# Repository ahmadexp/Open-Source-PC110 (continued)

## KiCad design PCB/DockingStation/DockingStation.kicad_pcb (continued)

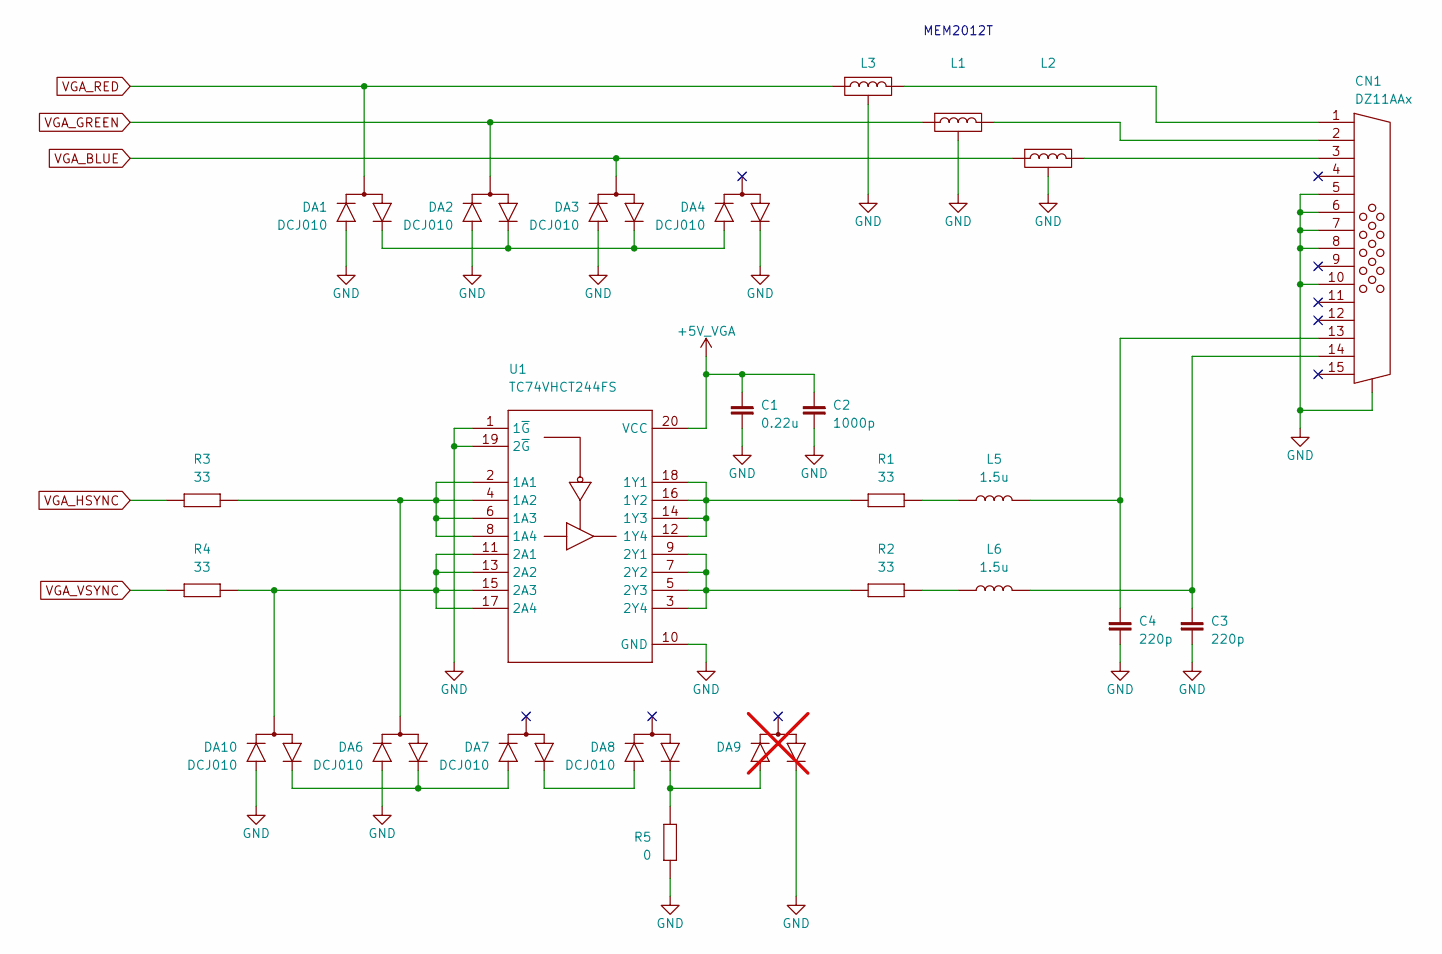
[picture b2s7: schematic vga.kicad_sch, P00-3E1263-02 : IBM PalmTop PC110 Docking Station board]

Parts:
C1: 0.22u
C2: 1000p
C3, C4: 220p
CN1: DZ11AAx
DA1, DA2, DA3, DA4, DA6, DA7, DA8, DA10: DCJ010
DA9: not fitted
L1, L2, L3: (no value)
L5, L6: 1.5u
R1, R2, R3, R4: 33
R5: 0
U1: TC74VHCT244FS

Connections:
+5V_VGA: C1.2, C2.2, U1.20 (VCC); also elsewhere on the board
GND: C1.1, C2.1, C3.2, C4.2, CN1.0, CN1.5, CN1.6, CN1.7, CN1.8, CN1.10, DA1.1 (A), DA2.1 (A), DA3.1 (A), DA4.2 (C), DA6.1 (A), DA9.2 (C), DA10.1 (A), L1.3, L2.3, L3.3, R5.1, U1.1 (1~G), U1.10 (GND), U1.19 (2~G); also elsewhere on the board
unnamed: C3.1, CN1.14, L6.2
unnamed: C4.1, CN1.13, L5.2
unnamed: CN1.1, L3.2
unnamed: CN1.2, L1.2
unnamed: CN1.3, L2.2
unnamed: DA1.2 (C), DA2.2 (C), DA3.2 (C), DA4.1 (A)
unnamed: DA6.3 (CA), R3.2, U1.2 (1A1), U1.4 (1A2), U1.6 (1A3), U1.8 (1A4)
unnamed: DA7.2 (C), DA8.1 (A)
unnamed: DA8.2 (C), DA9.1 (A), R5.2
unnamed: DA6.2 (C), DA7.1 (A), DA10.2 (C)
unnamed: DA10.3 (CA), R4.2, U1.11 (2A1), U1.13 (2A2), U1.15 (2A3), U1.17 (2A4)
unnamed: L5.1, R1.2
unnamed: L6.1, R2.2
unnamed: R1.1, U1.12 (1Y4), U1.14 (1Y3), U1.16 (1Y2), U1.18 (1Y1)
unnamed: R2.1, U1.3 (2Y4), U1.5 (2Y3), U1.7 (2Y2), U1.9 (2Y1)
VGA_BLUE: DA3.3 (CA), L2.1; also elsewhere on the board
VGA_GREEN: DA2.3 (CA), L1.1; also elsewhere on the board
VGA_HSYNC: R3.1; also elsewhere on the board
VGA_RED: DA1.3 (CA), L3.1; also elsewhere on the board
VGA_VSYNC: R4.1; also elsewhere on the board

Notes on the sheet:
MEM2012T

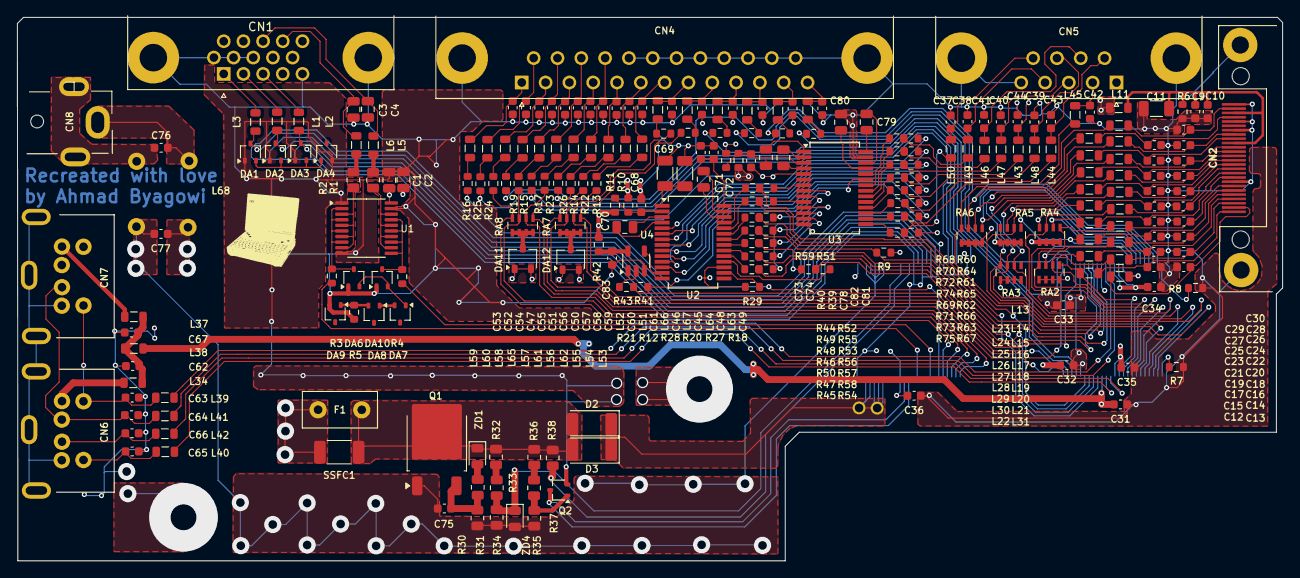
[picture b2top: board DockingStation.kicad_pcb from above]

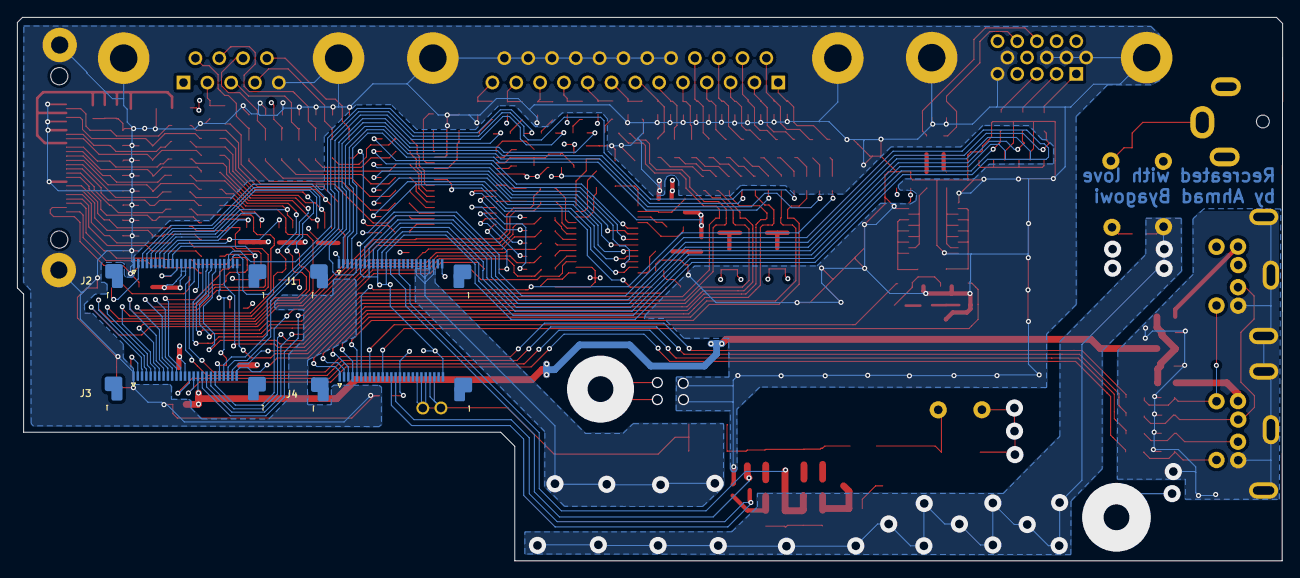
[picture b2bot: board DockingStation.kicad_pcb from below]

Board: 4 copper layers, 147.2 x 63.2 mm, 254 parts (4 on the bottom side), 220 nets.

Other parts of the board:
G1: LOGO; logo

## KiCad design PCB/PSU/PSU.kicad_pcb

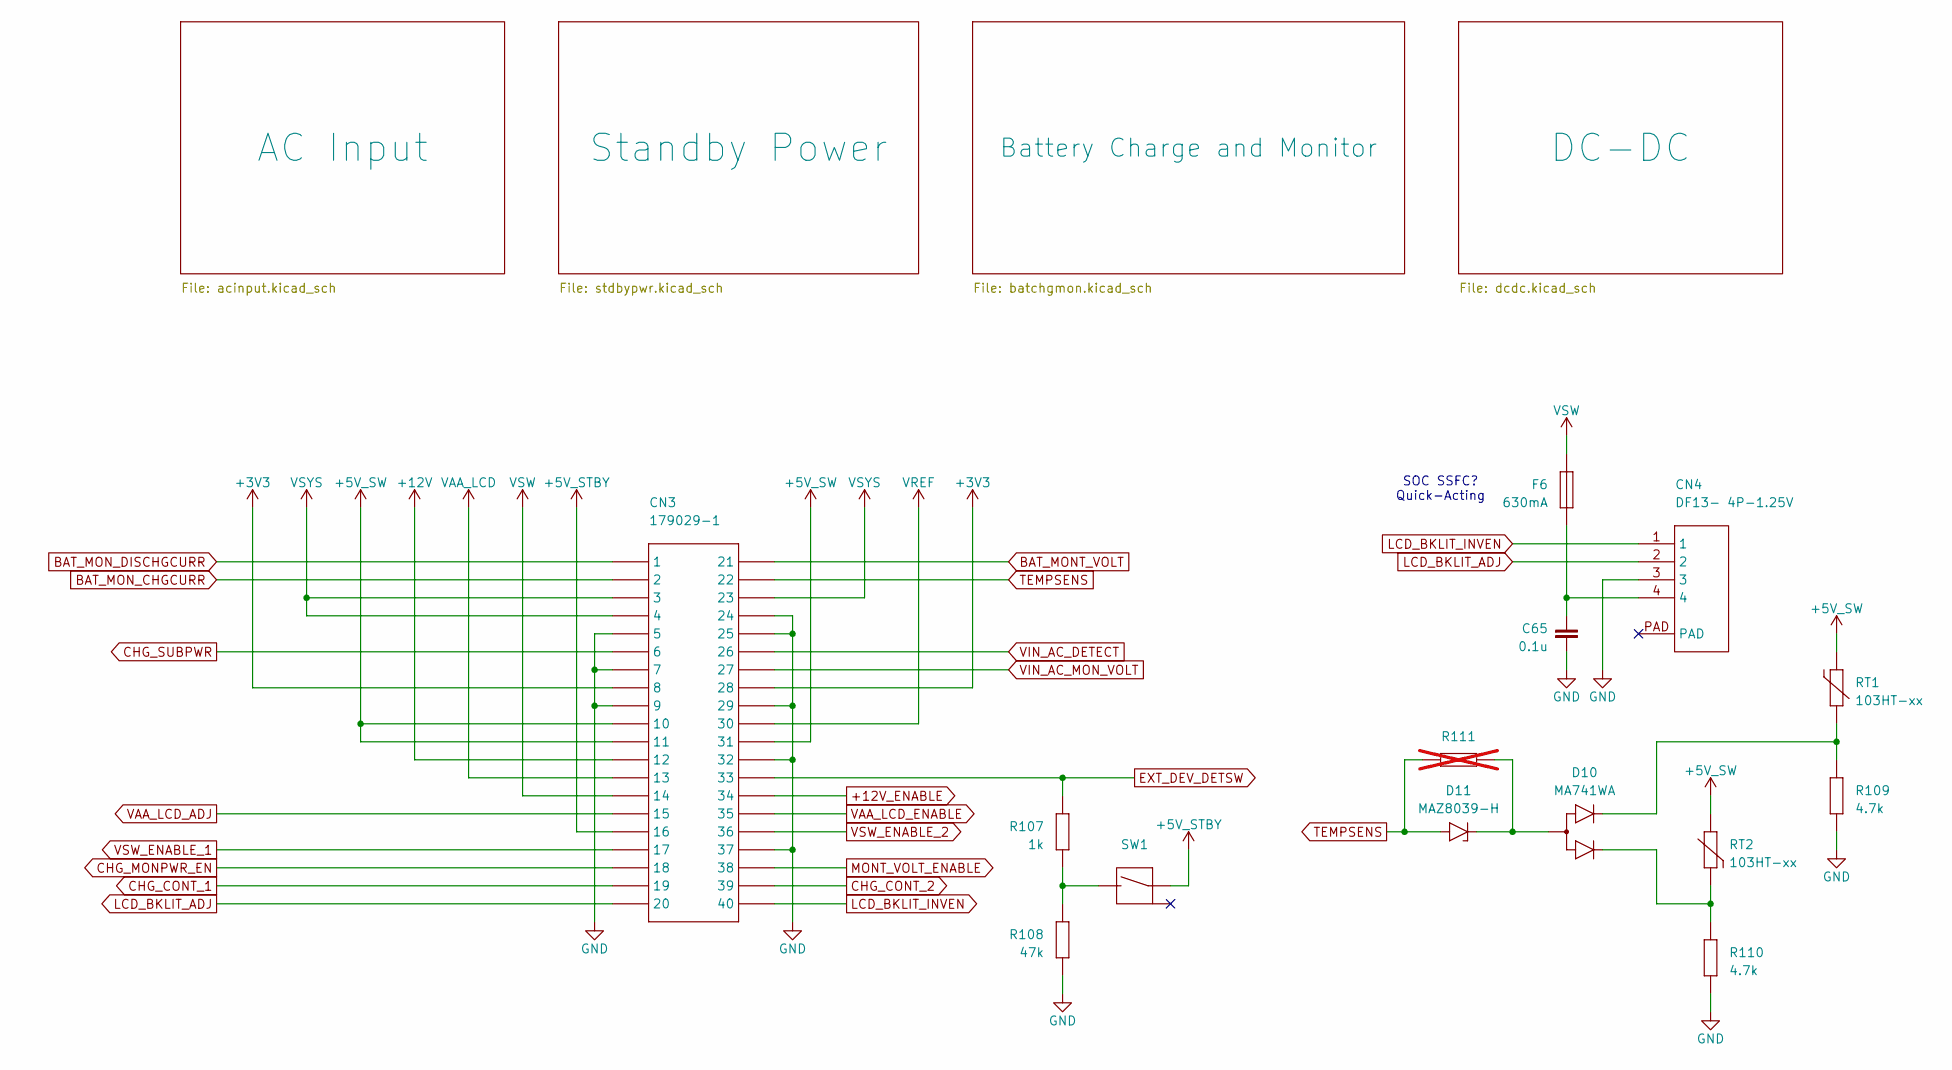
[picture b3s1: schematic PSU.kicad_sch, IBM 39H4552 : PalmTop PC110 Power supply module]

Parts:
C65: 0.1u
CN3: 179029-1
CN4: DF13- 4P-1.25V
D10: MA741WA
D11: MAZ8039-H
F6: 630mA
R107: 1k
R108: 47k
R109, R110: 4.7k
R111: not fitted
RT1, RT2: 103HT-xx
SW1: (no value)

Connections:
+3V3: CN3.8, CN3.28; also elsewhere on the board
+5V_STBY: CN3.16, SW1.1; also elsewhere on the board
+5V_SW: CN3.10, CN3.11, CN3.31, RT1.2, RT2.1; also elsewhere on the board
+12V: CN3.12; also elsewhere on the board
+12V_ENABLE: CN3.34; also elsewhere on the board
BAT_MONT_VOLT: CN3.21; also elsewhere on the board
BAT_MON_CHGCURR: CN3.2; also elsewhere on the board
BAT_MON_DISCHGCURR: CN3.1; also elsewhere on the board
CHG_CONT_1: CN3.19; also elsewhere on the board
CHG_CONT_2: CN3.39; also elsewhere on the board
CHG_MONPWR_EN: CN3.18; also elsewhere on the board
CHG_SUBPWR: CN3.6; also elsewhere on the board
EXT_DEV_DETSW: CN3.33, R107.2; also elsewhere on the board
GND: C65.1, CN3.5, CN3.7, CN3.9, CN3.24, CN3.25, CN3.29, CN3.32, CN3.37, CN4.3, R108.2, R109.1, R110.1; also elsewhere on the board
LCD_BKLIT_ADJ: CN3.20, CN4.2
LCD_BKLIT_INVEN: CN3.40, CN4.1
MONT_VOLT_ENABLE: CN3.38; also elsewhere on the board
unnamed: C65.2, CN4.4, F6.1
unnamed: D10.2 (A), D11.1 (C), R111.1
unnamed: D10.1 (C1), R110.2, RT2.2
unnamed: D10.3 (C2), R109.2, RT1.1
unnamed: R107.1, R108.1, SW1.2
TEMPSENS: CN3.22, D11.2 (A), R111.2
VAA_LCD: CN3.13; also elsewhere on the board
VAA_LCD_ADJ: CN3.15; also elsewhere on the board
VAA_LCD_ENABLE: CN3.35; also elsewhere on the board
VIN_AC_DETECT: CN3.26; also elsewhere on the board
VIN_AC_MON_VOLT: CN3.27; also elsewhere on the board
VREF: CN3.30; also elsewhere on the board
VSW: CN3.14, F6.2; also elsewhere on the board
VSW_ENABLE_1: CN3.17; also elsewhere on the board
VSW_ENABLE_2: CN3.36; also elsewhere on the board
VSYS: CN3.3, CN3.4, CN3.23; also elsewhere on the board

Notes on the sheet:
SOC SSFC? Quick-Acting

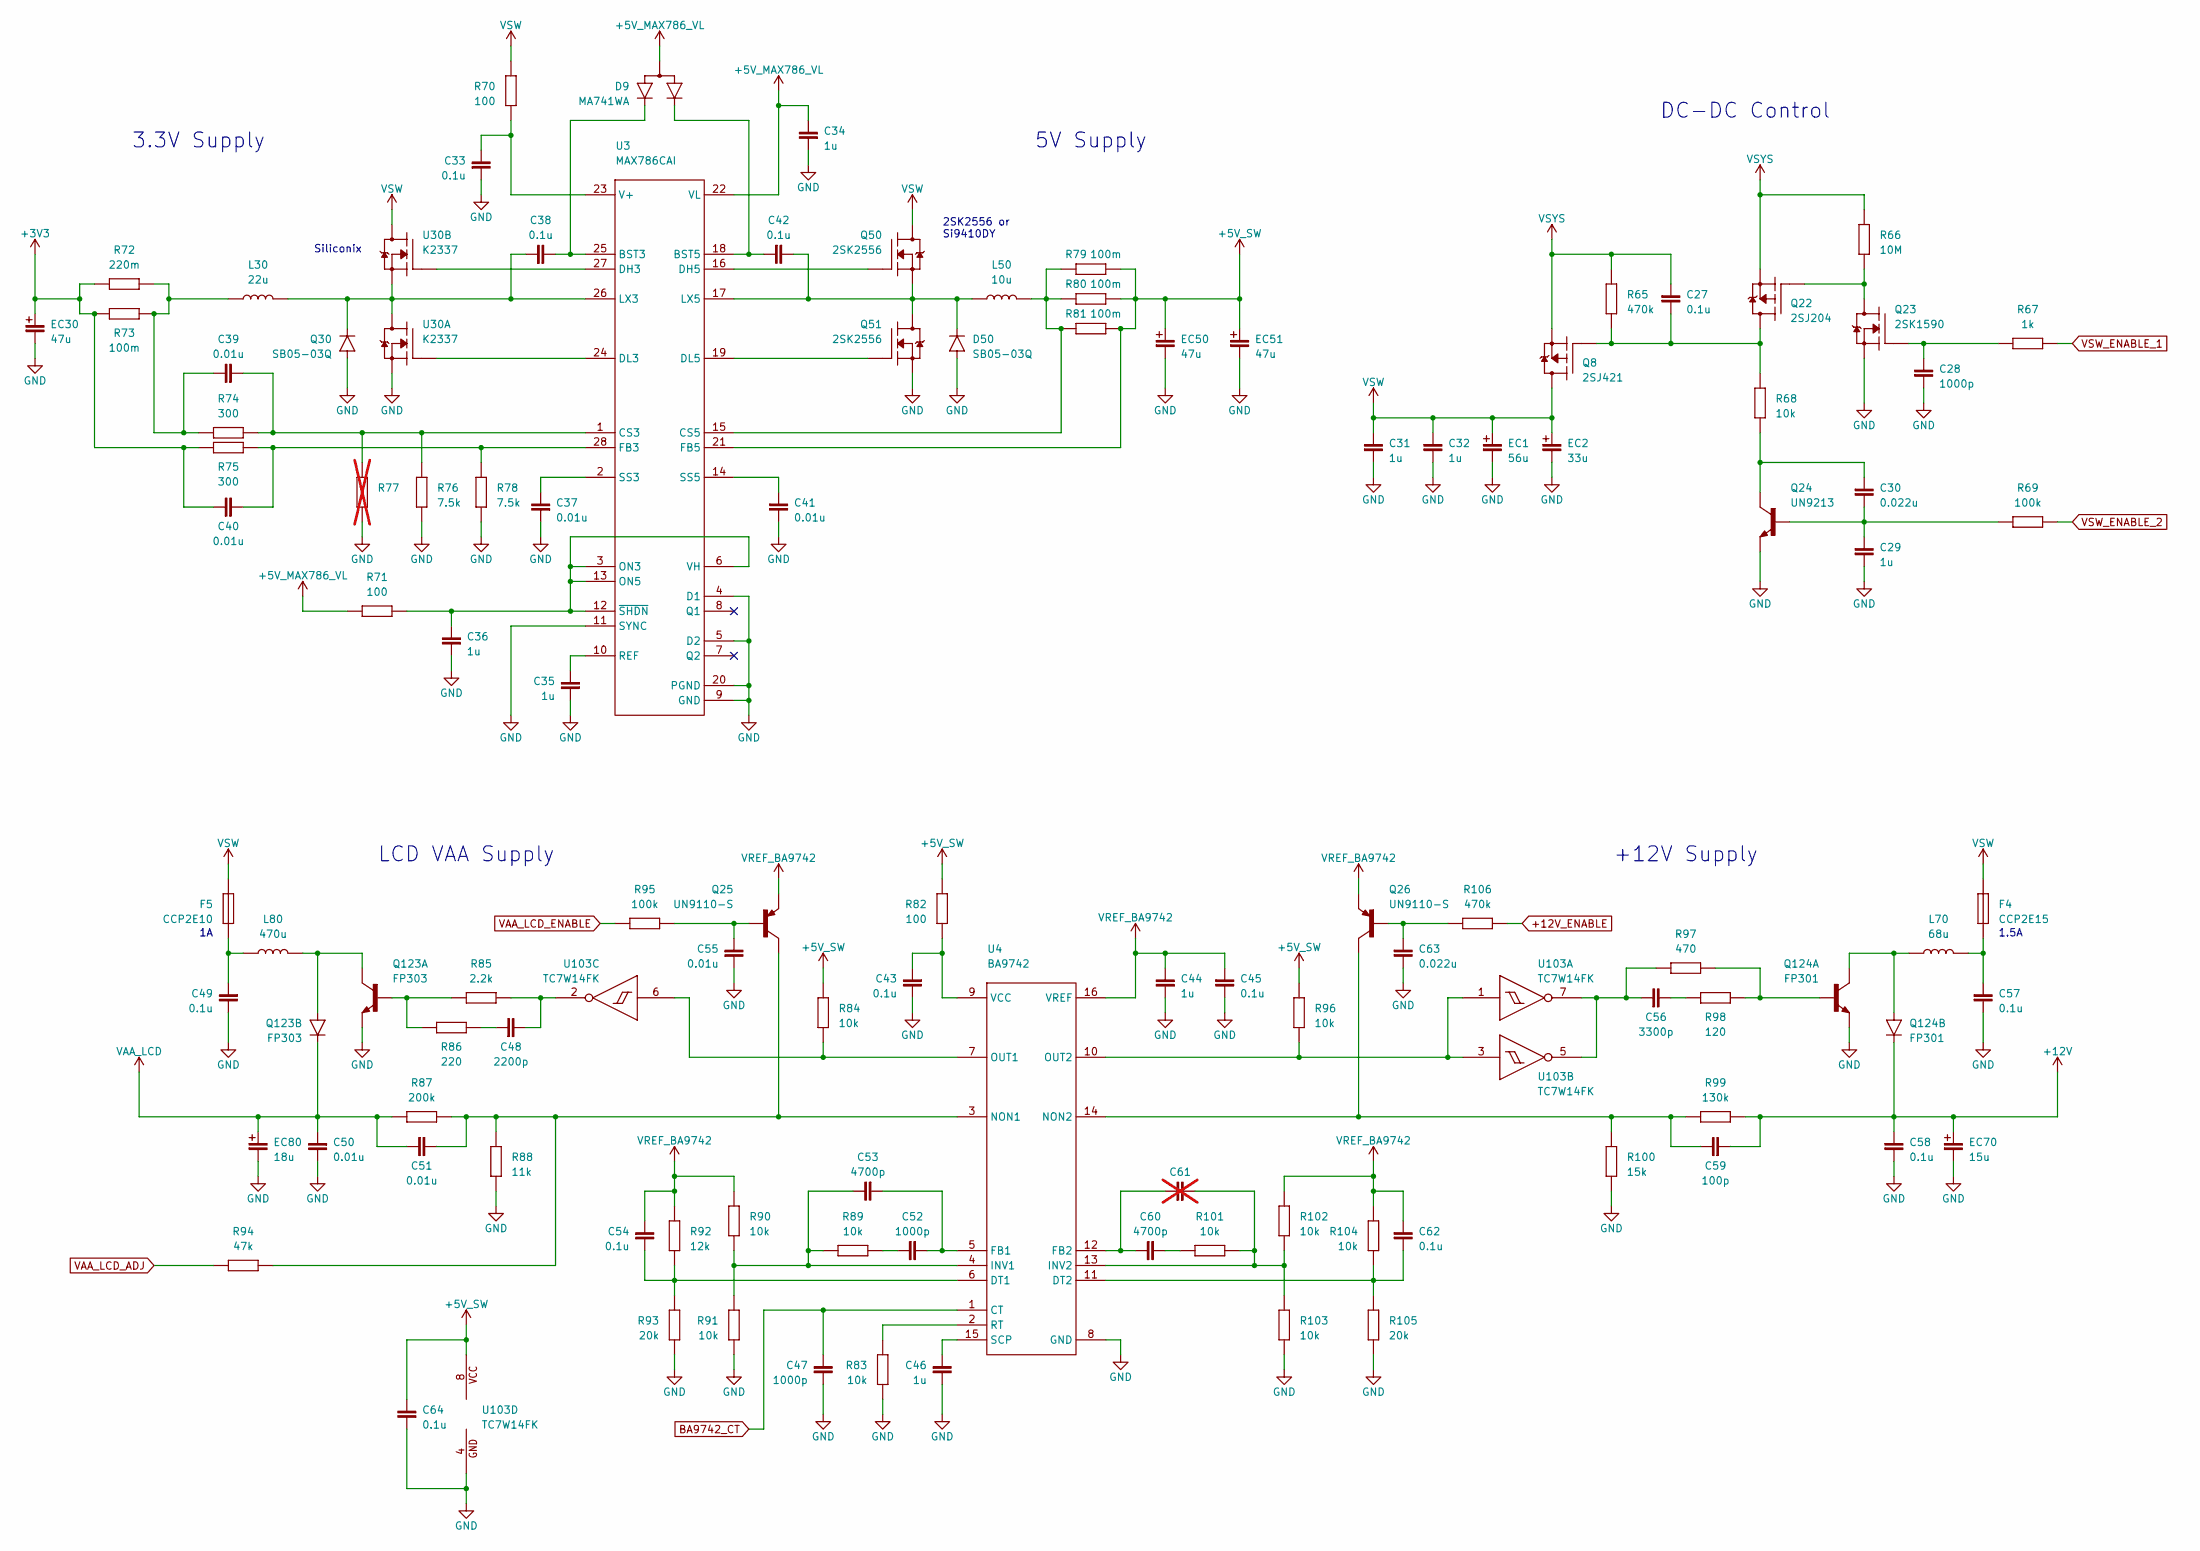
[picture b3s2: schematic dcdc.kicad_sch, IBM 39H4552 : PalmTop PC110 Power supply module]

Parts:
C27, C33, C38, C42, C43, C45, C49, C54, C57, C58, C62, C64: 0.1u
C28, C47, C52: 1000p
C29, C31, C32, C34, C35, C36, C44, C46: 1u
C30, C63: 0.022u
C37, C39, C40, C41, C50, C51, C55: 0.01u
C48: 2200p
C53, C60: 4700p
C56: 3300p
C59: 100p
C61: not fitted
D9: MA741WA
D50: SB05-03Q
EC1: 56u
EC2: 33u
EC30, EC50, EC51: 47u
EC70: 15u
EC80: 18u
F4: CCP2E15
F5: CCP2E10
L30: 22u
L50: 10u
L70: 68u
L80: 470u
Q8: 2SJ421
Q22: 2SJ204
Q23: 2SK1590
Q24: UN9213
Q25, Q26: UN9110-S
Q30: SB05-03Q
Q50, Q51: 2SK2556
Q123: FP303
Q124: FP301
R65, R106: 470k
R66: 10M
R67: 1k
R68, R83, R84, R89, R90, R91, R96, R101, R102, R103, R104: 10k
R69, R95: 100k
R70, R71, R82: 100
R72: 220m
R73, R79, R80, R81: 100m
R74, R75: 300
R76, R78: 7.5k
R77: not fitted
R85: 2.2k
R86: 220
R87: 200k
R88: 11k
R92: 12k
R93, R105: 20k
R94: 47k
R97: 470
R98: 120
R99: 130k
R100: 15k
U3: MAX786CAI
U4: BA9742
U30: K2337
U103: TC7W14FK

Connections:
+3V3: C40.1, EC30.2 (1), R72.1, R73.1, R75.1; also elsewhere on the board
+5V_MAX786_VL: C34.2, D9.2 (A), R71.1, U3.22 (VL)
+5V_SW: C64.2, EC50.2 (1), EC51.2 (1), R79.1, R80.1, R81.1, R82.1, R84.2, R96.2, U3.21 (FB5), U103.8 (VCC); also elsewhere on the board
+12V: C58.1, C59.2, EC70.2 (1), Q124.4 (C), R99.2; also elsewhere on the board
+12V_ENABLE: R106.2; also elsewhere on the board
BA9742_CT: C47.2, U4.1 (CT); also elsewhere on the board
GND: C28.2, C29.2, C31.2, C32.2, C33.1, C34.1, C35.2, C36.1, C37.1, C41.2, C43.2, C44.1, C45.2, C46.1, C47.1, C49.2, C50.1, C55.1, C57.2, C58.2, C63.2, C64.1, D50.1 (A), D50.3 (A), EC1.1 (2), EC2.1 (2), EC30.1 (2), EC50.1 (2), EC51.1 (2), EC70.1 (2), EC80.1 (2), Q23.2 (S), Q24.2 (E), Q30.1 (A), Q30.3 (A), Q51.1 (S), Q51.2 (S), Q51.3 (S), Q123.2 (E), Q124.2 (E), R76.1, R77.1, R78.2, R83.2, R88.2, R91.2, R93.1, R100.1, R103.2, R105.2, U3.4 (D1), U3.5 (D2), U3.9 (GND), U3.11 (SYNC), U3.20 (PGND), U4.8 (GND), U30.1 (S), U103.4 (GND); also elsewhere on the board
unnamed: C39.1, L30.2, R72.2, R73.2, R74.1
unnamed: C48.1, R86.2
unnamed: C49.1, F5.1, L80.2
unnamed: C52.2, R89.2
unnamed: C56.2, R98.2
unnamed: C57.1, F4.1, L70.1
unnamed: C60.1, R101.1
unnamed: C42.2, D9.1 (C1), U3.18 (BST5)
unnamed: C38.2, D9.3 (C2), U3.25 (BST3)
unnamed: C42.1, D50.2 (C), L50.2, Q50.1 (S), Q50.2 (S), Q50.3 (S), Q51.5 (D), Q51.6 (D), Q51.7 (D), Q51.8 (D), U3.17 (LX5)
unnamed: C27.2, Q8.4 (G), Q22.3 (D), R65.2, R68.1
unnamed: Q22.1 (G), Q23.3 (D), R66.1
unnamed: C28.1, Q23.1 (G), R67.1
unnamed: C29.1, C30.2, Q24.1 (B), R69.1
unnamed: C30.1, Q24.3 (C), R68.2
unnamed: C55.2, Q25.1 (B), R95.2
unnamed: C51.1, Q25.3 (C), R87.1, R88.1, R94.1, U4.3 (NON1)
unnamed: C63.1, Q26.1 (B), R106.1
unnamed: C59.1, Q26.3 (C), R99.1, R100.2, U4.14 (NON2)
unnamed: C38.1, L30.1, Q30.2 (C), U3.26 (LX3), U30.3 (S), U30.7 (D), U30.8 (D)
unnamed: Q50.4 (G), U3.16 (DH5)
unnamed: Q51.4 (G), U3.19 (DL5)
unnamed: Q123.1 (B), R85.1, R86.1
unnamed: L80.1, Q123.3 (A), Q123.5 (C)
unnamed: Q124.1 (B), R97.1, R98.1
unnamed: L70.2, Q124.3 (A), Q124.5 (C)
unnamed: C39.2, R74.2, R76.2, R77.2, U3.1 (CS3)
unnamed: L50.1, R79.2, R80.2, R81.2, U3.15 (CS5)
unnamed: U3.27 (DH3), U30.4 (G)
unnamed: U3.24 (DL3), U30.2 (G)
unnamed: C40.2, R75.2, R78.1, U3.28 (FB3)
unnamed: C36.2, R71.2, U3.3 (ON3), U3.6 (VH), U3.12 (~SHDN), U3.13 (ON5)
unnamed: C35.1, U3.10 (REF)
unnamed: C37.2, U3.2 (SS3)
unnamed: C41.1, U3.14 (SS5)
unnamed: C33.2, R70.1, U3.23 (V+)
unnamed: C54.1, R92.2, R93.2, U4.6 (DT1)
unnamed: C62.2, R104.1, R105.1, U4.11 (DT2)
unnamed: C52.1, C53.1, U4.5 (FB1)
unnamed: C60.2, C61.1, U4.12 (FB2)
unnamed: C53.2, R89.1, R90.2, R91.1, U4.4 (INV1)
unnamed: C61.2, R101.2, R102.1, R103.1, U4.13 (INV2)
unnamed: R83.1, U4.2 (RT)
unnamed: C46.2, U4.15 (SCP)
unnamed: C43.1, R82.2, U4.9 (VCC)
unnamed: R96.1, U4.10 (OUT2), U103.1 (1A), U103.3 (2A)
unnamed: C56.1, R97.2, U103.5 (2Y), U103.7 (1Y)
unnamed: R84.1, U4.7 (OUT1), U103.6 (3A)
unnamed: C48.2, R85.2, U103.2 (3Y)
VAA_LCD: C50.2, C51.2, EC80.2 (1), Q123.4 (C), R87.2; also elsewhere on the board
VAA_LCD_ADJ: R94.2; also elsewhere on the board
VAA_LCD_ENABLE: R95.1; also elsewhere on the board
VREF_BA9742: C44.2, C45.1, C54.2, C62.1, Q25.2 (E), Q26.2 (E), R90.1, R92.1, R102.2, R104.2, U4.16 (VREF)
VSW: C31.1, C32.1, EC1.2 (1), EC2.2 (1), F4.2, F5.2, Q8.5 (D), Q8.6 (D), Q8.7 (D), Q8.8 (D), Q50.5 (D), Q50.6 (D), Q50.7 (D), Q50.8 (D), R70.2, U30.5 (D), U30.6 (D); also elsewhere on the board
VSW_ENABLE_1: R67.2; also elsewhere on the board
VSW_ENABLE_2: R69.2; also elsewhere on the board
VSYS: C27.1, Q8.1 (S), Q8.2 (S), Q8.3 (S), Q22.2 (S), R65.1, R66.2; also elsewhere on the board

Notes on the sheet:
3.3V Supply
LCD VAA Supply
2SK2556 or Si9410DY
Siliconix
DC-DC Control
5V Supply
1.5A
+12V Supply

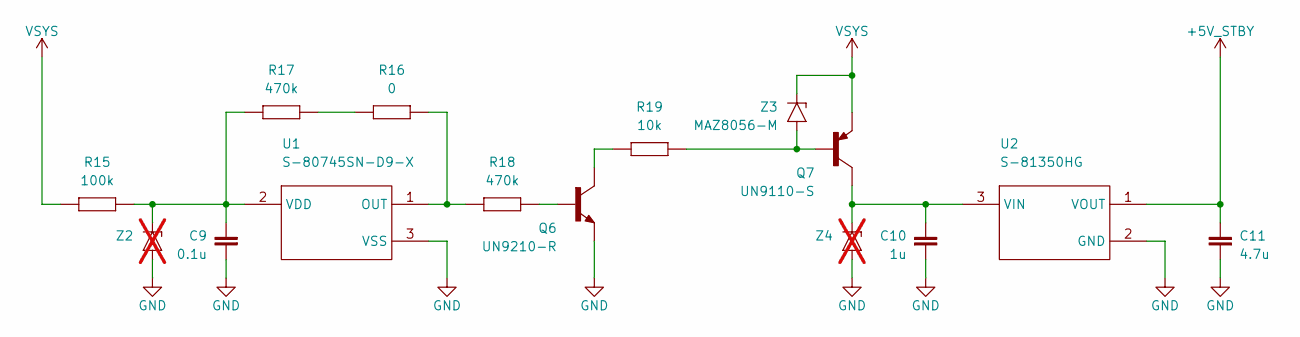
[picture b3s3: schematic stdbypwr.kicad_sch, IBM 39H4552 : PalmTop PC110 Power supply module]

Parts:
C9: 0.1u
C10: 1u
C11: 4.7u
Q6: UN9210-R
Q7: UN9110-S
R15: 100k
R16: 0
R17, R18: 470k
R19: 10k
U1: S-80745SN-D9-X
U2: S-81350HG
Z2, Z4: not fitted
Z3: MAZ8056-M

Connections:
+5V_STBY: C11.2, U2.1 (VOUT); also elsewhere on the board
GND: C9.2, C10.1, C11.1, Q6.2 (E), U1.3 (VSS), U2.2 (GND), Z2.2 (A), Z4.2 (A); also elsewhere on the board
unnamed: Q6.1 (B), R18.1
unnamed: Q6.3 (C), R19.1
unnamed: Q7.1 (B), R19.2, Z3.2 (A)
unnamed: C10.2, Q7.3 (C), U2.3 (VIN), Z4.1 (C)
unnamed: R16.2, R17.2
unnamed: R16.1, R18.2, U1.1 (OUT)
unnamed: C9.1, R15.1, R17.1, U1.2 (VDD), Z2.1 (C)
VSYS: Q7.2 (E), R15.2, Z3.1 (C); also elsewhere on the board

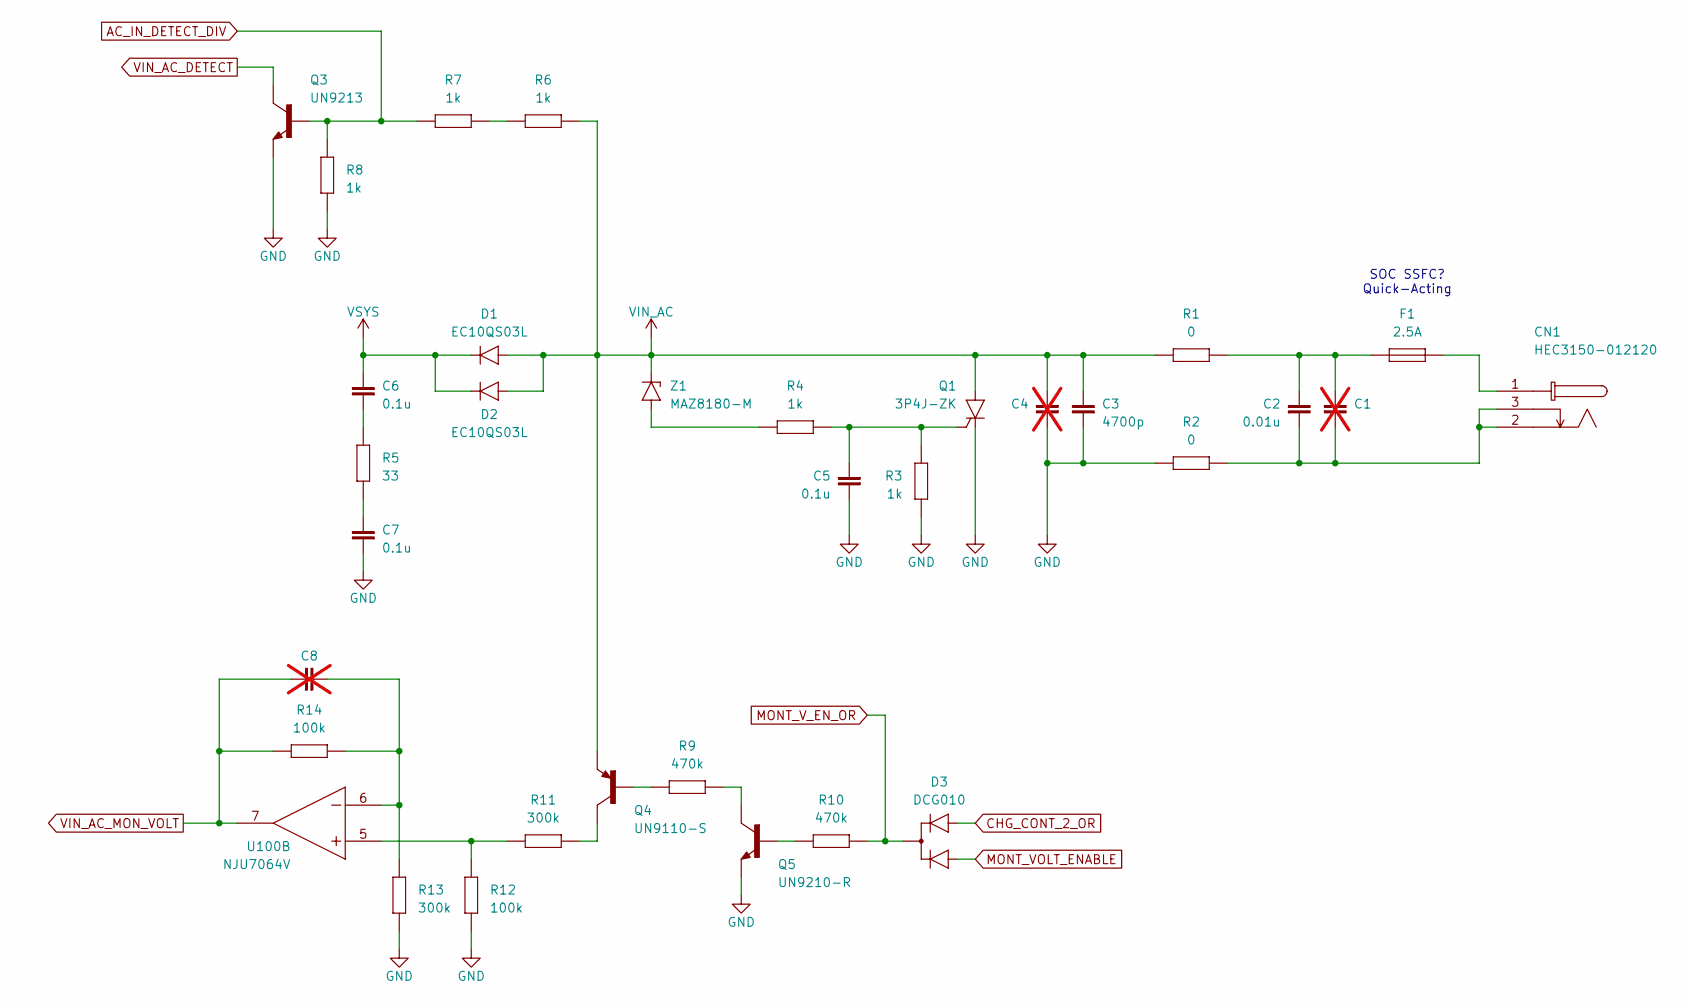
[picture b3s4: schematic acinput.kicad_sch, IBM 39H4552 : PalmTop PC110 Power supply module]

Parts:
C1, C4, C8: not fitted
C2: 0.01u
C3: 4700p
C5, C6, C7: 0.1u
CN1: HEC3150-012120
D1, D2: EC10QS03L
D3: DCG010
F1: 2.5A
Q1: 3P4J-ZK
Q3: UN9213
Q4: UN9110-S
Q5: UN9210-R
R1, R2: 0
R3, R4, R6, R7, R8: 1k
R5: 33
R9, R10: 470k
R11, R13: 300k
R12, R14: 100k
U100: NJU7064V
Z1: MAZ8180-M

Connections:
AC_IN_DETECT_DIV: Q3.1 (B), R7.2, R8.2; also elsewhere on the board
CHG_CONT_2_OR: D3.3 (A2); also elsewhere on the board
GND: C3.1, C4.2, C5.2, C7.1, Q1.1 (C), Q3.2 (E), Q5.2 (E), R2.2, R3.2, R8.1, R12.2, R13.1; also elsewhere on the board
MONT_VOLT_ENABLE: D3.1 (A1); also elsewhere on the board
MONT_V_EN_OR: D3.2 (C), R10.1
unnamed: C1.1, C2.2, F1.1, R1.1
unnamed: C1.2, C2.1, CN1.2, CN1.3, R2.1
unnamed: C6.1, R5.2
unnamed: C7.2, R5.1
unnamed: CN1.1, F1.2
unnamed: C5.1, Q1.3 (G), R3.1, R4.2
unnamed: Q4.1 (B), R9.1
unnamed: Q4.3 (C), R11.2
unnamed: Q5.1 (B), R10.2
unnamed: Q5.3 (C), R9.2
unnamed: R6.1, R7.1
unnamed: R11.1, R12.1, U100.5 (2IN+)
unnamed: C8.2, R13.2, R14.2, U100.6 (2IN-)
unnamed: R4.1, Z1.2 (A)
VIN_AC: C3.2, C4.1, D1.2 (A), D2.2 (A), Q1.2 (A), Q4.2 (E), R1.2, R6.2, Z1.1 (C); also elsewhere on the board
VIN_AC_DETECT: Q3.3 (C); also elsewhere on the board
VIN_AC_MON_VOLT: C8.1, R14.1, U100.7 (2OUT); also elsewhere on the board
VSYS: C6.2, D1.1 (C), D2.1 (C); also elsewhere on the board

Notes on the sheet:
SOC SSFC? Quick-Acting

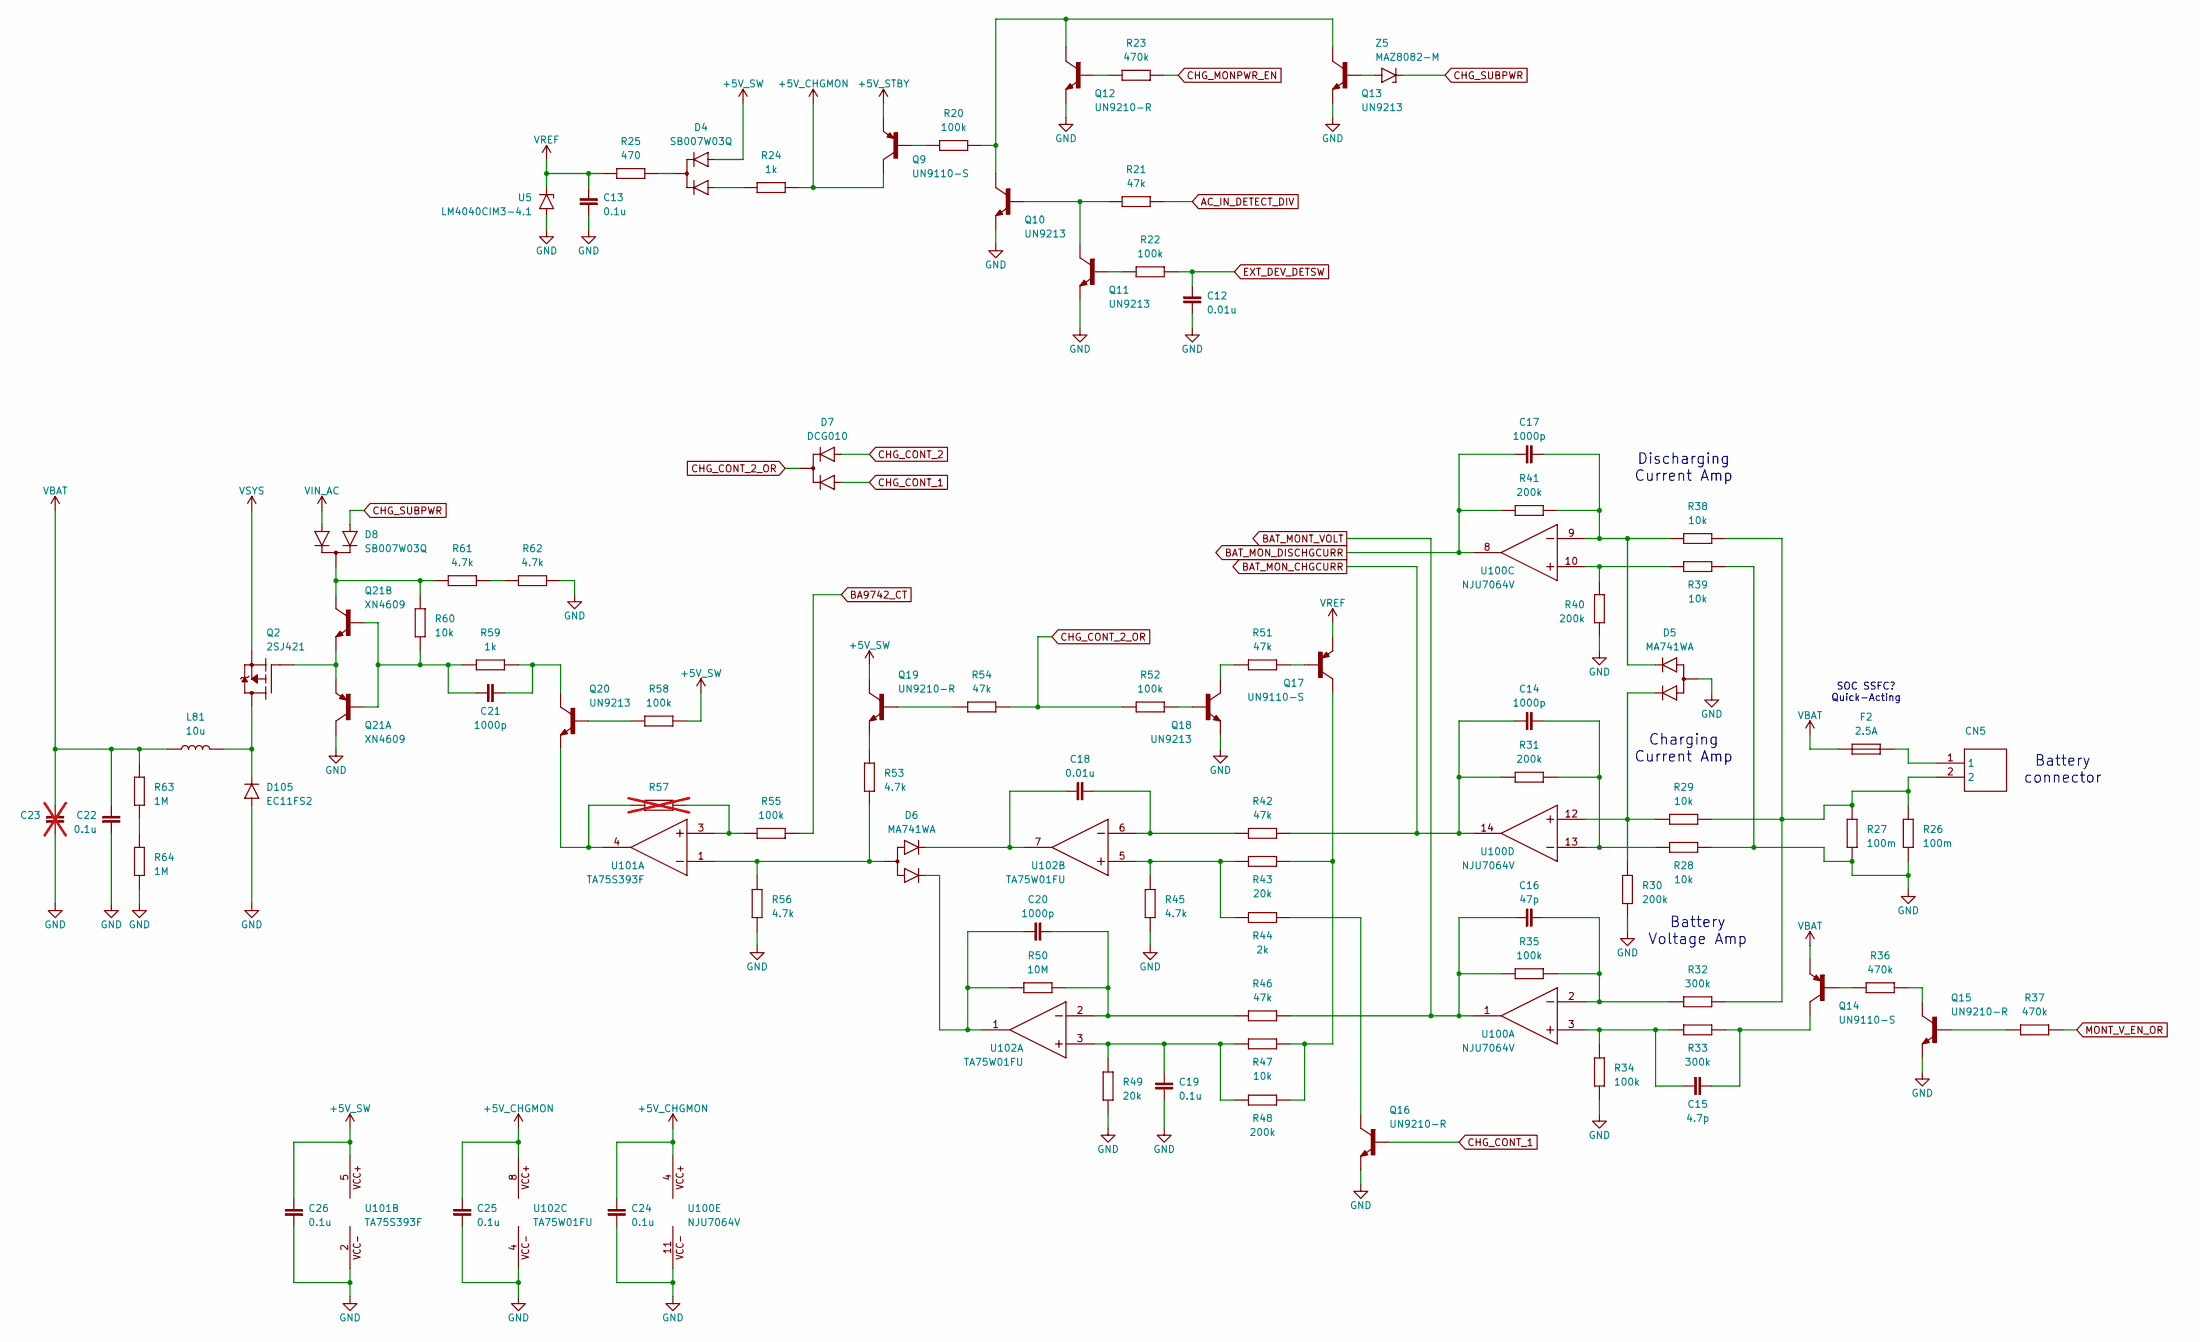
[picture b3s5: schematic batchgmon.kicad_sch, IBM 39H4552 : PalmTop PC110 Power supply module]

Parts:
C12, C18: 0.01u
C13, C19, C22, C24, C25, C26: 0.1u
C14, C17, C20, C21: 1000p
C15: 4.7p
C16: 47p
C23: not fitted
CN5: (no value)
D4, D8: SB007W03Q
D5, D6: MA741WA
D7: DCG010
D105: EC11FS2
F2: 2.5A
L81: 10u
Q2: 2SJ421
Q9, Q14, Q17: UN9110-S
Q10, Q11, Q13, Q18, Q20: UN9213
Q12, Q15, Q16, Q19: UN9210-R
Q21: XN4609
R20, R22, R34, R35, R52, R55, R58: 100k
R21, R42, R46, R51, R54: 47k
R23, R36, R37: 470k
R24, R59: 1k
R25: 470
R26, R27: 100m
R28, R29, R38, R39, R47, R60: 10k
R30, R31, R40, R41, R48: 200k
R32, R33: 300k
R43, R49: 20k
R44: 2k
R45, R53, R56, R61, R62: 4.7k
R50: 10M
R57: not fitted
R63, R64: 1M
U5: LM4040CIM3-4.1
U100: NJU7064V
U101: TA75S393F
U102: TA75W01FU
Z5: MAZ8082-M

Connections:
+5V_CHGMON: C24.1, C25.1, Q9.3 (C), R24.1, U100.4 (VCC+), U102.8 (VCC+)
+5V_STBY: Q9.2 (E); also elsewhere on the board
+5V_SW: C26.2, D4.3 (A2), Q19.3 (C), R58.2, U101.5 (VCC+); also elsewhere on the board
AC_IN_DETECT_DIV: R21.1; also elsewhere on the board
BA9742_CT: R55.1; also elsewhere on the board
BAT_MONT_VOLT: C16.1, R35.1, R46.2, U100.1 (1OUT); also elsewhere on the board
BAT_MON_CHGCURR: C14.1, R31.1, R42.1, U100.14 (4OUT); also elsewhere on the board
BAT_MON_DISCHGCURR: C17.1, R41.1, U100.8 (3OUT); also elsewhere on the board
CHG_CONT_1: D7.1 (A1), Q16.1 (B); also elsewhere on the board
CHG_CONT_2: D7.3 (A2); also elsewhere on the board
CHG_CONT_2_OR: D7.2 (C), R52.2, R54.2; also elsewhere on the board
CHG_MONPWR_EN: R23.1; also elsewhere on the board
CHG_SUBPWR: D8.1 (A1), Z5.1 (C); also elsewhere on the board
EXT_DEV_DETSW: C12.1, R22.1; also elsewhere on the board
GND: C12.2, C13.1, C19.2, C22.1, C23.1, C24.2, C25.2, C26.1, D5.2 (A), D105.2 (A), Q10.2 (E), Q11.2 (E), Q12.2 (E), Q13.2 (E), Q15.2 (E), Q16.2 (E), Q18.2 (E), Q21.3 (Q1_C), R26.1, R27.1, R28.1, R30.2, R34.2, R39.1, R40.1, R45.2, R49.2, R56.2, R62.2, R64.1, U5.1 (A), U100.11 (VCC-), U101.2 (VCC-), U102.4 (VCC-); also elsewhere on the board
unnamed: CN5.1, F2.1
unnamed: CN5.2, R26.2, R27.2, R29.2, R32.1, R38.2
unnamed: D4.1 (A1), R24.2
unnamed: D4.2 (C), R25.2
unnamed: D5.1 (C1), R29.1, R30.1, U100.12 (4IN+)
unnamed: C17.2, D5.3 (C2), R38.1, R41.2, U100.9 (3IN-)
unnamed: D6.2 (A), R53.1, R56.1, U101.1 (1IN-)
unnamed: C20.2, D6.1 (C1), R50.2, U102.1 (1OUT)
unnamed: C18.2, D6.3 (C2), U102.7 (2OUT)
unnamed: D8.2 (C), Q21.6 (Q2_C), R60.2, R61.1
unnamed: D105.1 (C), L81.2, Q2.5 (D), Q2.6 (D), Q2.7 (D), Q2.8 (D)
unnamed: Q2.4 (G), Q21.1 (Q2_E), Q21.4 (Q1_E)
unnamed: Q9.1 (B), R20.1
unnamed: Q10.1 (B), Q11.3 (C), R21.2
unnamed: Q10.3 (C), Q12.3 (C), Q13.3 (C), R20.2
unnamed: Q11.1 (B), R22.2
unnamed: Q12.1 (B), R23.2
unnamed: Q13.1 (B), Z5.2 (A)
unnamed: Q14.1 (B), R36.2
unnamed: C15.2, Q14.3 (C), R33.2
unnamed: Q15.1 (B), R37.1
unnamed: Q15.3 (C), R36.1
unnamed: Q16.3 (C), R44.2
unnamed: Q17.1 (B), R51.1
unnamed: Q17.3 (C), R43.2, R47.2, R48.2
unnamed: Q18.1 (B), R52.1
unnamed: Q18.3 (C), R51.2
unnamed: Q19.1 (B), R54.1
unnamed: Q19.2 (E), R53.2
unnamed: Q20.1 (B), R58.1
unnamed: C21.2, Q20.3 (C), R59.1
unnamed: Q20.2 (E), R57.1, U101.4 (1OUT)
unnamed: C21.1, Q21.2 (Q2_B), Q21.5 (Q1_B), R59.2, R60.1
unnamed: R61.2, R62.1
unnamed: R63.1, R64.2
unnamed: C15.1, R33.1, R34.1, U100.3 (1IN+)
unnamed: C16.2, R32.2, R35.2, U100.2 (1IN-)
unnamed: R39.2, R40.2, U100.10 (3IN+)
unnamed: C14.2, R28.2, R31.2, U100.13 (4IN-)
unnamed: R55.2, R57.2, U101.3 (1IN+)
unnamed: C19.1, R47.1, R48.1, R49.1, U102.3 (1IN+)
unnamed: C20.1, R46.1, R50.1, U102.2 (1IN-)
unnamed: R43.1, R44.1, R45.1, U102.5 (2IN+)
unnamed: C18.1, R42.2, U102.6 (2IN-)
VBAT: C22.2, C23.2, F2.2, L81.1, Q14.2 (E), R63.2
VIN_AC: D8.3 (A2); also elsewhere on the board
VREF: C13.2, Q17.2 (E), R25.1, U5.3 (C); also elsewhere on the board
VSYS: Q2.1 (S), Q2.2 (S), Q2.3 (S); also elsewhere on the board

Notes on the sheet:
Charging Current Amp
Battery connector
SOC SSFC? Quick-Acting
Discharging Current Amp
Battery Voltage Amp
